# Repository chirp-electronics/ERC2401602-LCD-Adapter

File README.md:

# Adapter board for ERC240160-2 Series LCD

This is an adapter board for a 3.4inch Graphic LCD display from [BuyDisplay](https://www.buydisplay.com/3-4-inch-graphic-touchscreen-lcd-cog-module-240x160-single-sided-fpc).

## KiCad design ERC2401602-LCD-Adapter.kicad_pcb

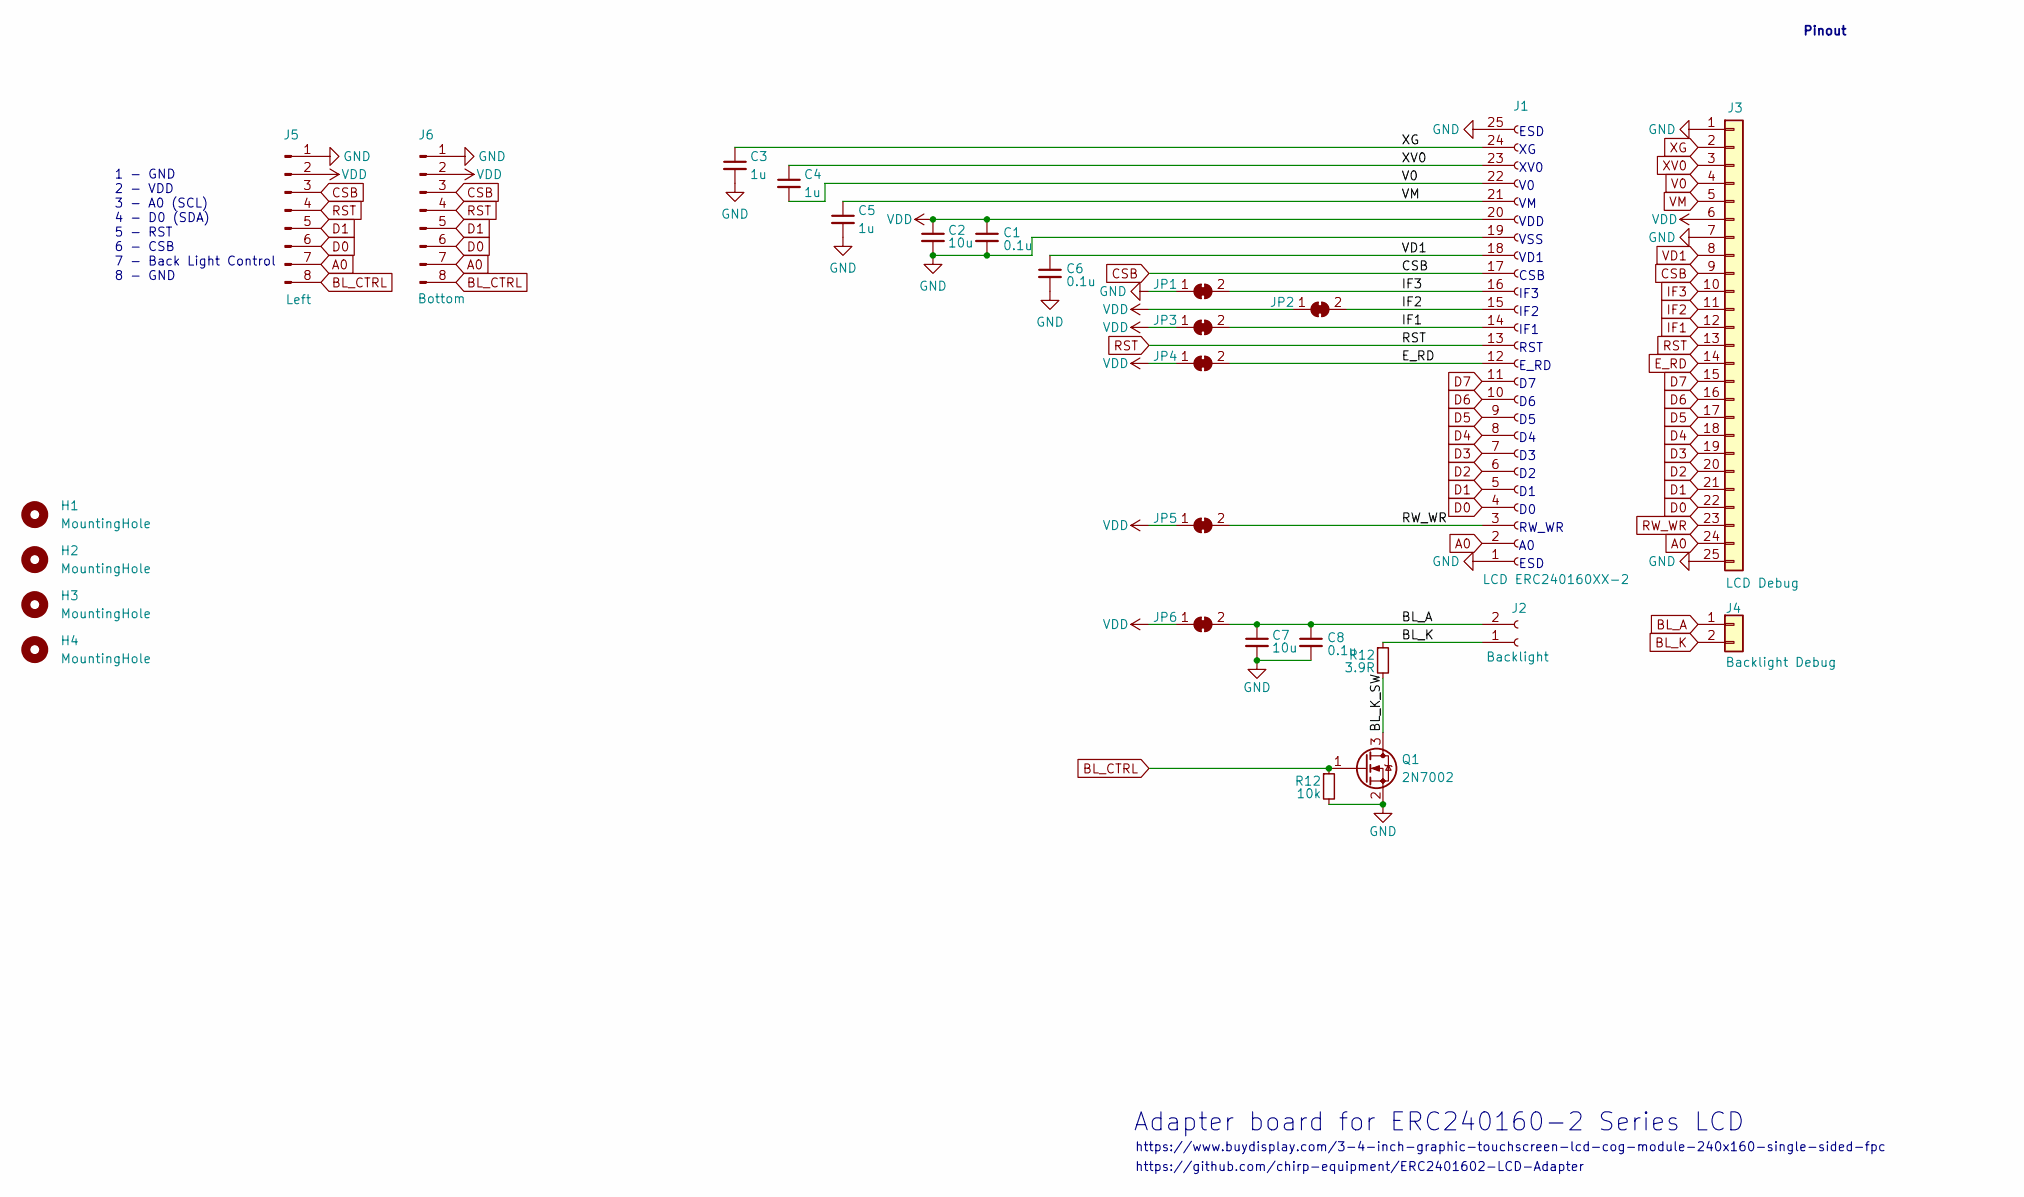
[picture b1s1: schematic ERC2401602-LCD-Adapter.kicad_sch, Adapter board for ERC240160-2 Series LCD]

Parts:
C1, C6, C8: 0.1u; C_0603_1608Metric_Pad1.08x0.95mm_HandSolder; LCSC C14663
C2, C7: 10u; C_0805_2012Metric_Pad1.18x1.45mm_HandSolder; LCSC C440198
C3, C4, C5: 1u; C_0603_1608Metric_Pad1.08x0.95mm_HandSolder; LCSC C15849
H1, H2, H3, H4: MountingHole; MountingHole_2.7mm_M2.5_ISO7380
J1: LCD ERC240160XX-2; TE_2-1734839-5_1x25-1MP_P0.5mm_Horizontal; LCSC C2911850
J2: Backlight; JST_PH_S2B-PH-SM4-TB_1x02-1MP_P2.00mm_Horizontal; LCSC C295747
J3: LCD Debug; PinHeader_1x25_P1.27mm_Vertical
J4: Backlight Debug; PinHeader_1x02_P1.27mm_Vertical
J5: Left; PinHeader_1x08_P2.54mm_Vertical
J6: Bottom; PinHeader_1x08_P2.54mm_Vertical
JP1: JP_IF3; SolderJumper-2_P1.3mm_Bridged_RoundedPad1.0x1.5mm
JP2: JP_IF2; SolderJumper-2_P1.3mm_Bridged_RoundedPad1.0x1.5mm
JP3: JP_IF1; SolderJumper-2_P1.3mm_Bridged_RoundedPad1.0x1.5mm
JP4: JP_E_RD; SolderJumper-2_P1.3mm_Bridged_RoundedPad1.0x1.5mm
JP5, JP6: JP_RW_WR; SolderJumper-2_P1.3mm_Bridged_RoundedPad1.0x1.5mm
Q1: 2N7002; SOT-23; LCSC C8545
R12: 3.9R; R_0603_1608Metric_Pad0.98x0.95mm_HandSolder; LCSC C2907146

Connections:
/BL_K_SW: Q1.3 (D); also elsewhere on the board
A0: J1.2, J3.24, J5.7, J6.7
BL_A: C7.1, C8.1, J2.2, J4.1, JP6.2 (B)
BL_CTRL: J5.8, J6.8, Q1.1 (G); also elsewhere on the board
BL_K: J2.1, J4.2; also elsewhere on the board
CSB: J1.17, J3.9, J5.3, J6.3
D0: J1.4, J3.22, J5.6, J6.6
D1: J1.5, J3.21, J5.5, J6.5
D2: J1.6, J3.20
D3: J1.7, J3.19
D4: J1.8, J3.18
D5: J1.9, J3.17
D6: J1.10, J3.16
D7: J1.11, J3.15
E_RD: J1.12, J3.14, JP4.2 (B)
GND: C1.2, C2.2, C3.2, C5.2, C6.2, C7.2, C8.2, J1.1, J1.19, J1.25, J3.1, J3.7, J3.25, J5.1, J6.1, JP1.1 (A), Q1.2 (S); also elsewhere on the board
IF1: J1.14, J3.12, JP3.2 (B)
IF2: J1.15, J3.11, JP2.2 (B)
IF3: J1.16, J3.10, JP1.2 (B)
RST: J1.13, J3.13, J5.4, J6.4
RW_WR: J1.3, J3.23, JP5.2 (B)
V0: C4.2, J1.22, J3.4
VD1: C6.1, J1.18, J3.8
VDD: C1.1, C2.1, J1.20, J3.6, J5.2, J6.2, JP2.1 (A), JP3.1 (A), JP4.1 (A), JP5.1 (A), JP6.1 (A)
VM: C5.1, J1.21, J3.5
XG: C3.1, J1.24, J3.2
XV0: C4.1, J1.23, J3.3

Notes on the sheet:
E_RD
IF1
https://www.buydisplay.com/3-4-inch-graphic-touchscreen-lcd-cog-module-240x160-single-sided-fpc
VSS
https://github.com/chirp-equipment/ERC2401602-LCD-Adapter
XV0
Adapter board for ERC240160-2 Series LCD
ESD
1 - GND 2 - VDD 3 - A0 (SCL) 4 - D0 (SDA) 5 - RST 6 - CSB 7 - Back Light Control 8 - GND
CSB
VDD
RST
IF2
Pinout
VD1
RW_WR
IF3

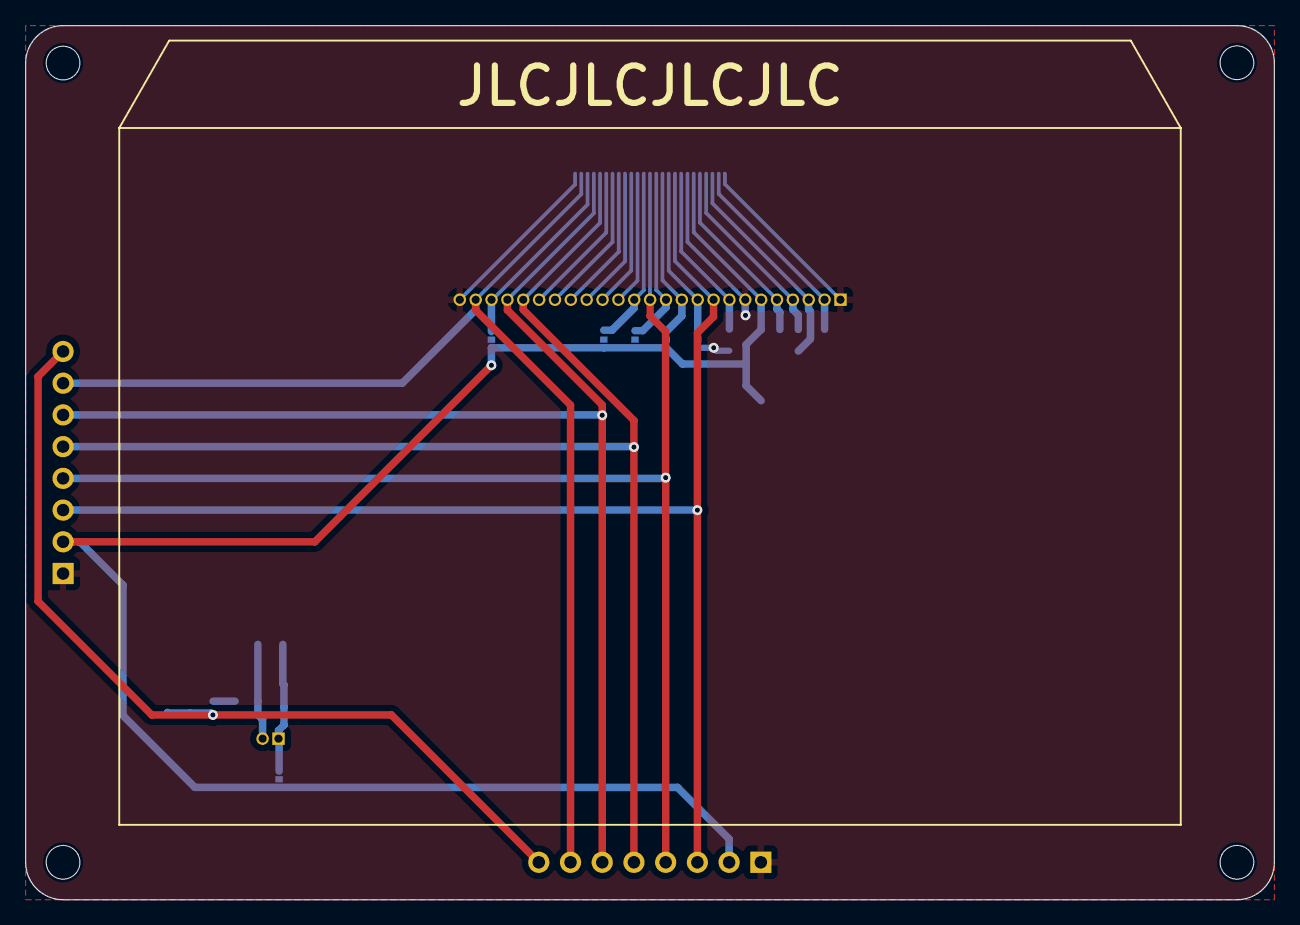
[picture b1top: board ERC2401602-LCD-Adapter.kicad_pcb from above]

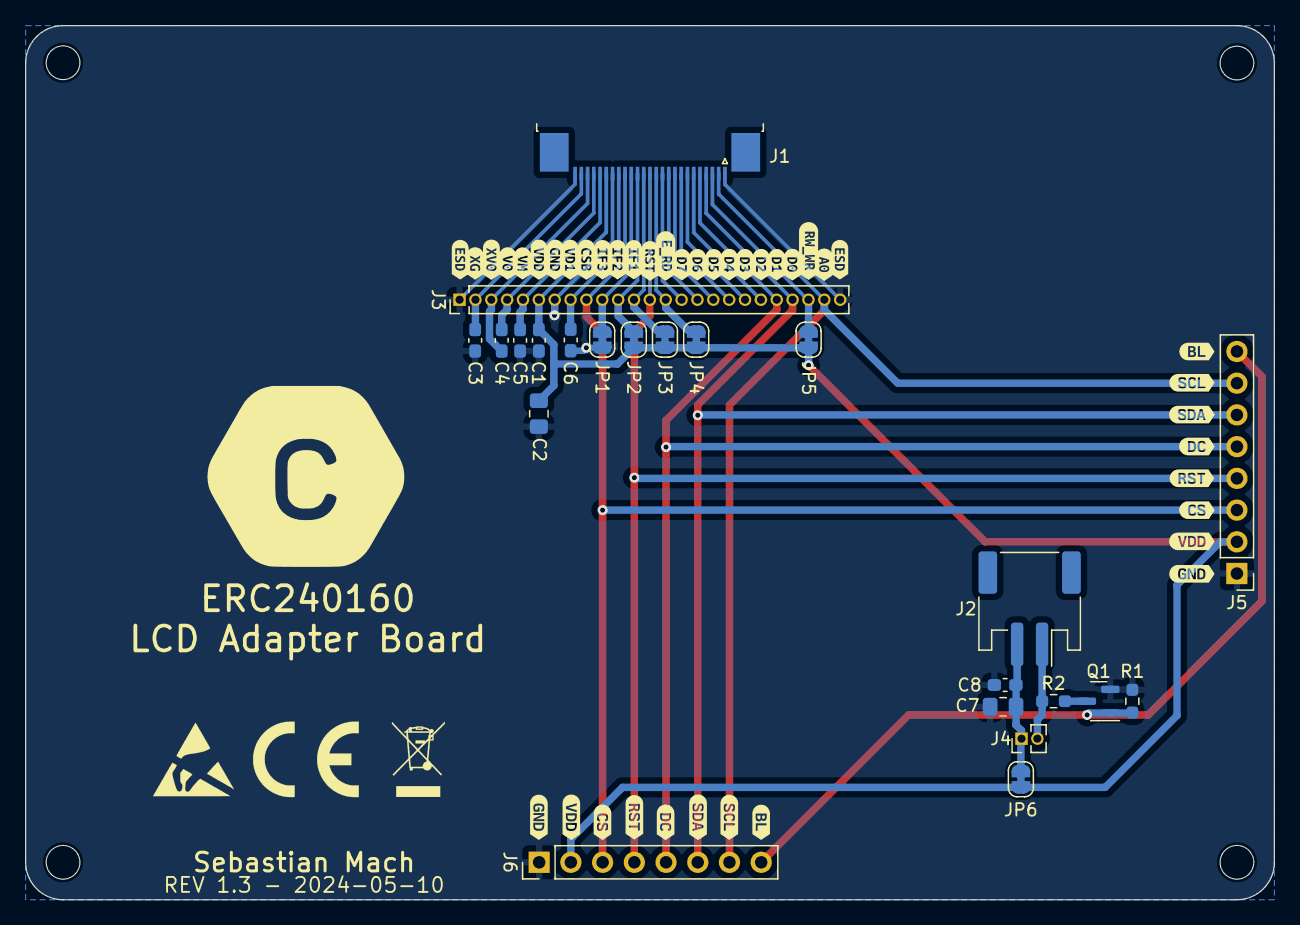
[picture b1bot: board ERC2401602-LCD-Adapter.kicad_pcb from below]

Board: 2 copper layers, 100.0 x 70.0 mm, 68 parts (64 on the bottom side), 27 nets.

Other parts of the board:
R1: 10k; R_0603_1608Metric_Pad0.98x0.95mm_HandSolder
R2: 3.9R; R_0603_1608Metric_Pad0.98x0.95mm_HandSolder
kibuzzard-658C9B5D, kibuzzard-658C9B5D#2: G***; kibuzzard-658C9B5D
kibuzzard-658C9B6D, kibuzzard-658C9B6D#2: G***; kibuzzard-658C9B6D
kibuzzard-658C9B20, kibuzzard-658C9B20#2: G***; kibuzzard-658C9B20
kibuzzard-658C9B55, kibuzzard-658C9B55#2: G***; kibuzzard-658C9B55
kibuzzard-658C9B67, kibuzzard-658C9B67#2: G***; kibuzzard-658C9B67
kibuzzard-658C9B71, kibuzzard-658C9B71#2: G***; kibuzzard-658C9B71
kibuzzard-658C9B93: G***; kibuzzard-658C9B93
kibuzzard-658C9CD2: G***; kibuzzard-658C9CD2
kibuzzard-658C9D0B: G***; kibuzzard-658C9D0B
kibuzzard-658C9D1B: G***; kibuzzard-658C9D1B
kibuzzard-658C9D2A: G***; kibuzzard-658C9D2A
kibuzzard-658C9D2F: G***; kibuzzard-658C9D2F
kibuzzard-658C9D3E: G***; kibuzzard-658C9D3E
kibuzzard-658C9D05: G***; kibuzzard-658C9D05
kibuzzard-658C9D5A: G***; kibuzzard-658C9D5A
kibuzzard-658C9D6A: G***; kibuzzard-658C9D6A
kibuzzard-658C9D6F: G***; kibuzzard-658C9D6F
kibuzzard-658C9D10: G***; kibuzzard-658C9D10
kibuzzard-658C9D14: G***; kibuzzard-658C9D14
kibuzzard-658C9D17: G***; kibuzzard-658C9D17
kibuzzard-658C9D20: G***; kibuzzard-658C9D20
kibuzzard-658C9D26: G***; kibuzzard-658C9D26
kibuzzard-658C9D34: G***; kibuzzard-658C9D34
kibuzzard-658C9D39: G***; kibuzzard-658C9D39
kibuzzard-658C9D44: G***; kibuzzard-658C9D44
kibuzzard-658C9D48: G***; kibuzzard-658C9D48
kibuzzard-658C9D52: G***; kibuzzard-658C9D52
kibuzzard-658C9D60: G***; kibuzzard-658C9D60
kibuzzard-658C9D64: G***; kibuzzard-658C9D64
kibuzzard-658C9D76: G***; kibuzzard-658C9D76
kibuzzard-658C9DA4: G***; kibuzzard-658C9DA4
kibuzzard-658C9DA9: G***; kibuzzard-658C9DA9
kibuzzard-663E4C9C, kibuzzard-663E4C9C#2: G***; kibuzzard-663E4C9C
kibuzzard-663E4C56: G***; kibuzzard-663E4C56

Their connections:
/BL_K_SW: R2.2; also elsewhere on the board
BL_CTRL: R1.1; also elsewhere on the board
BL_K: R2.1; also elsewhere on the board
GND: R1.2; also elsewhere on the board

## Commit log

2023-12-27 Rev 1.0
2023-12-28 Adding board2pdf config and improve gitignore
2023-12-28 Renamed files
2023-12-28 Added Footprints
2024-02-24 Fixed Resistor and BG Polarity
    - Changed the current limiting resistor value to 3.9R
    - Fixed the Background Light connector Polarity
    - Moved the LCD connector down 5mm
2024-05-10 Added DC PIN
2024-05-10 Adjusted trace with to 0.6
